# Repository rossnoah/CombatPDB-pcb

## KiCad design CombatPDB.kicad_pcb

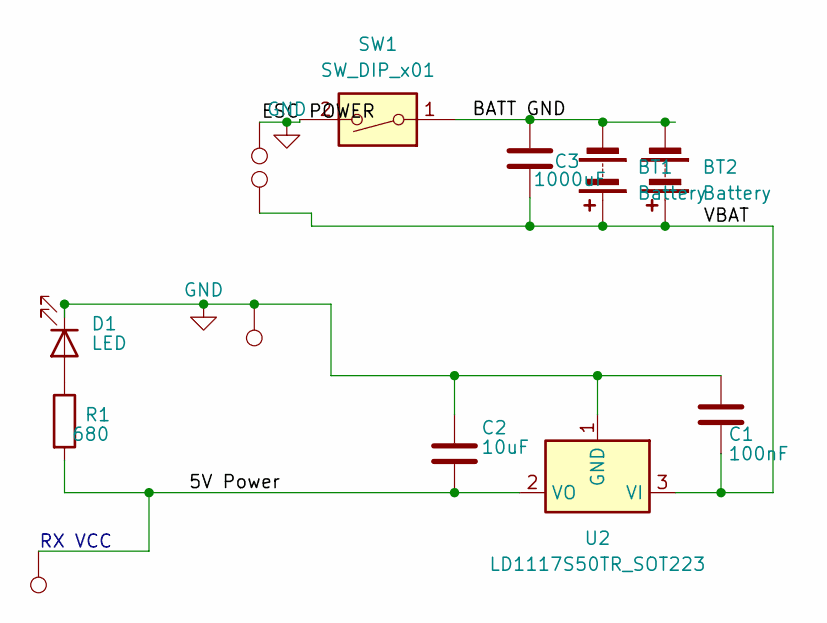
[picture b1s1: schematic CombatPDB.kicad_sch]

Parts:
BT1, BT2: Battery; XT30 Female
C1: 100nF; C_1206_3216Metric
C2: 10uF; C_1206_3216Metric
C3: 1000uF; Panasonic_FC-A_D10_L12_F5_CompactOverhang
D1: LED; LED_1206_3216Metric
R1: 680; R_1206_3216Metric
SW1: SW_DIP_x01; M4_Broaching_NutSwitch
TP1, TP7: TestPoint; TestPoint_Pad_1.5x1.5mm
TP3, TP6: TestPoint; TestPoint_Pad_3.0x9.0mm
U2: LD1117S50TR_SOT223; SOT-223-3_TabPin2

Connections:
/5V Power: C2.2, R1.2, TP7.1, U2.2 (VO)
/BATT GND: BT1.2 (-), BT2.2 (-), C3.1, SW1.1
/VBAT: BT1.1 (+), BT2.1 (+), C1.2, C3.2, TP6.1, U2.3 (VI)
GND: C1.1, C2.1, D1.1 (K), SW1.2, TP1.1, TP3.1, U2.1 (GND)
unnamed: D1.2 (A), R1.1

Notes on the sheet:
RX VCC

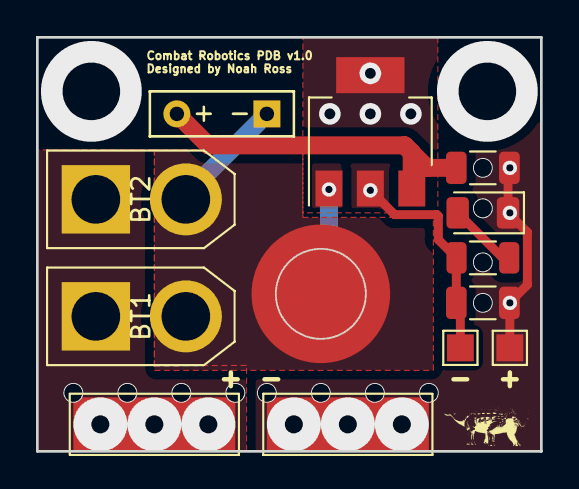
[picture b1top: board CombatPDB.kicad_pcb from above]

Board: 2 copper layers, 28.0 x 23.0 mm, 13 parts (0 on the bottom side), 5 nets.

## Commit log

2024-08-20 initial board design
2024-08-20 allow gbr files
2024-08-20 allow schematic and pcb
2024-08-20 disallow gbr
2024-08-20 remove gbrjob files
2024-08-20 remove exported gbrs
